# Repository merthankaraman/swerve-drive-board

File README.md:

# Swerve Drive Mobile Robot Board
### Schematic Of the Shield V2
<br/><br/>

### Board Of the Shield V2
<br/><br/>

### Schematic Of the Shield V1
<br/><br/>

### Board Of the Shield V1
<br/><br/>

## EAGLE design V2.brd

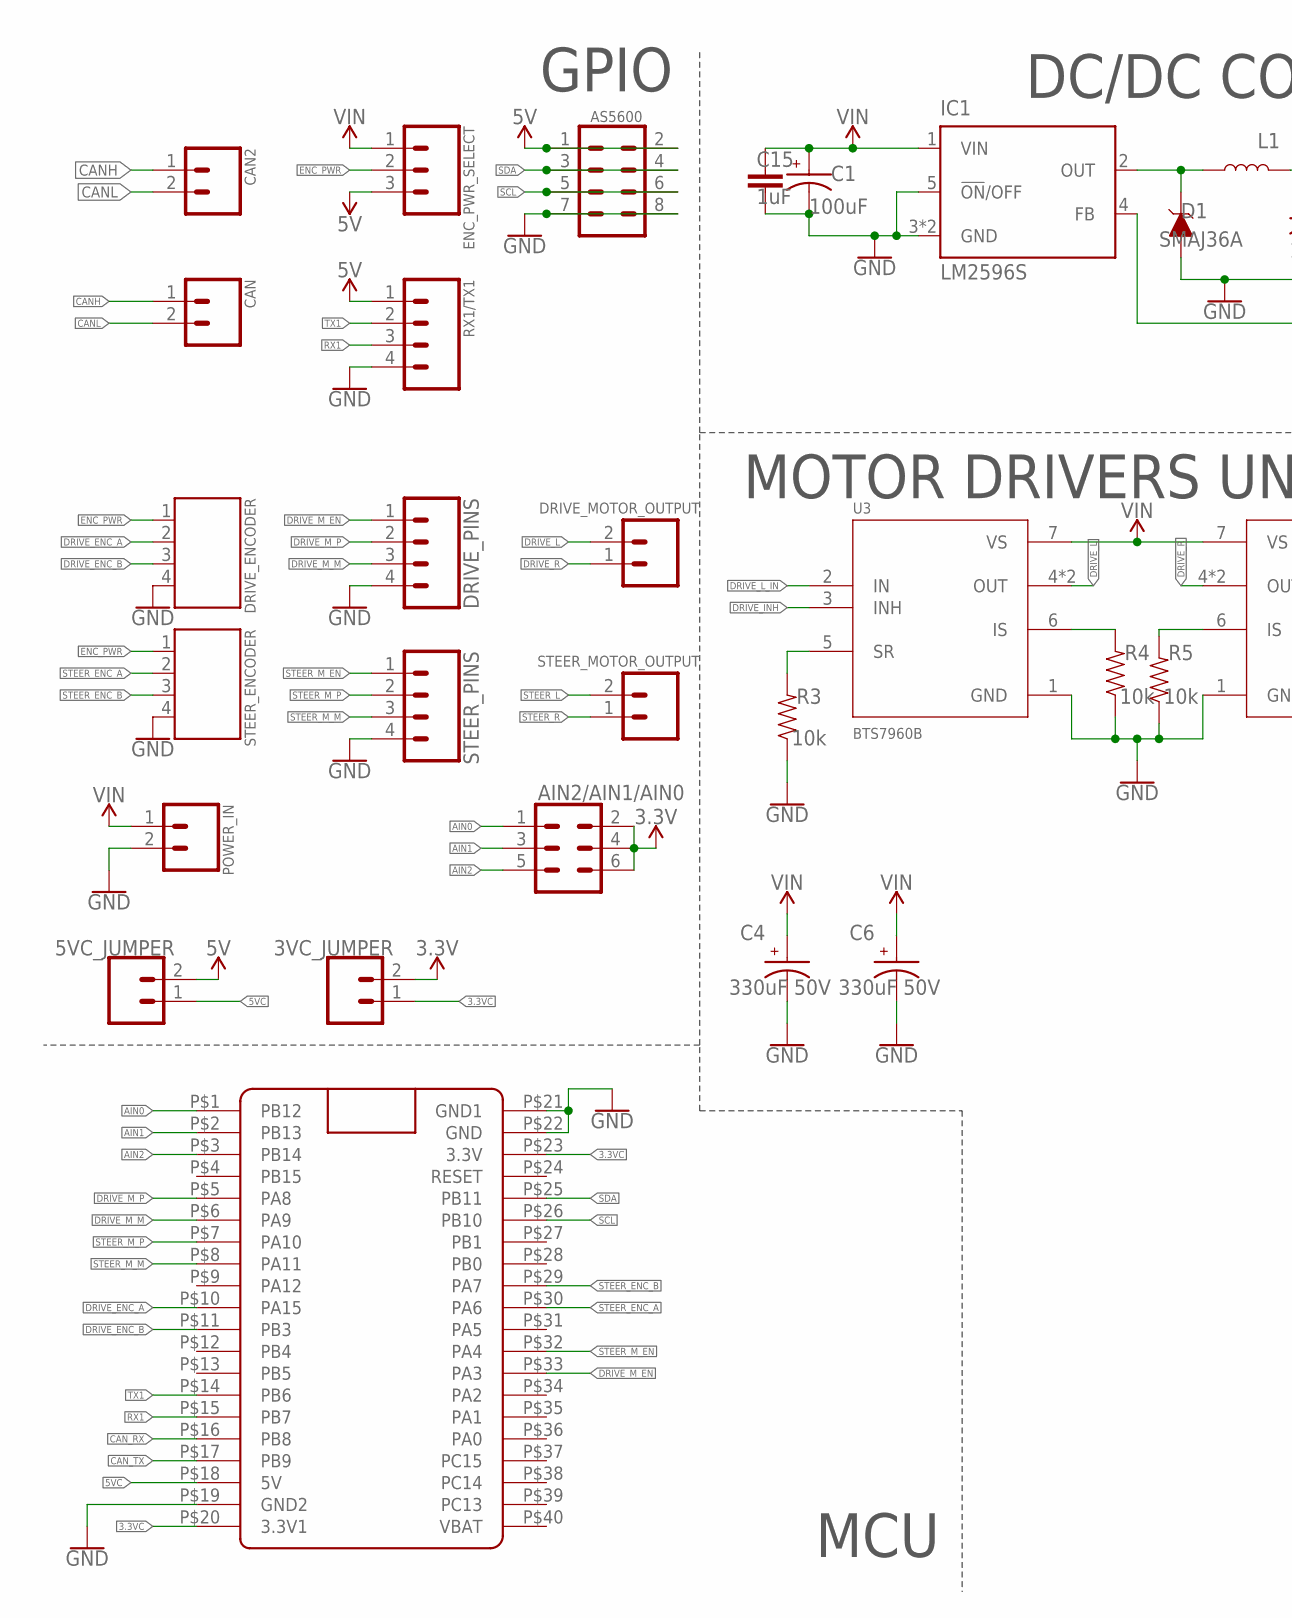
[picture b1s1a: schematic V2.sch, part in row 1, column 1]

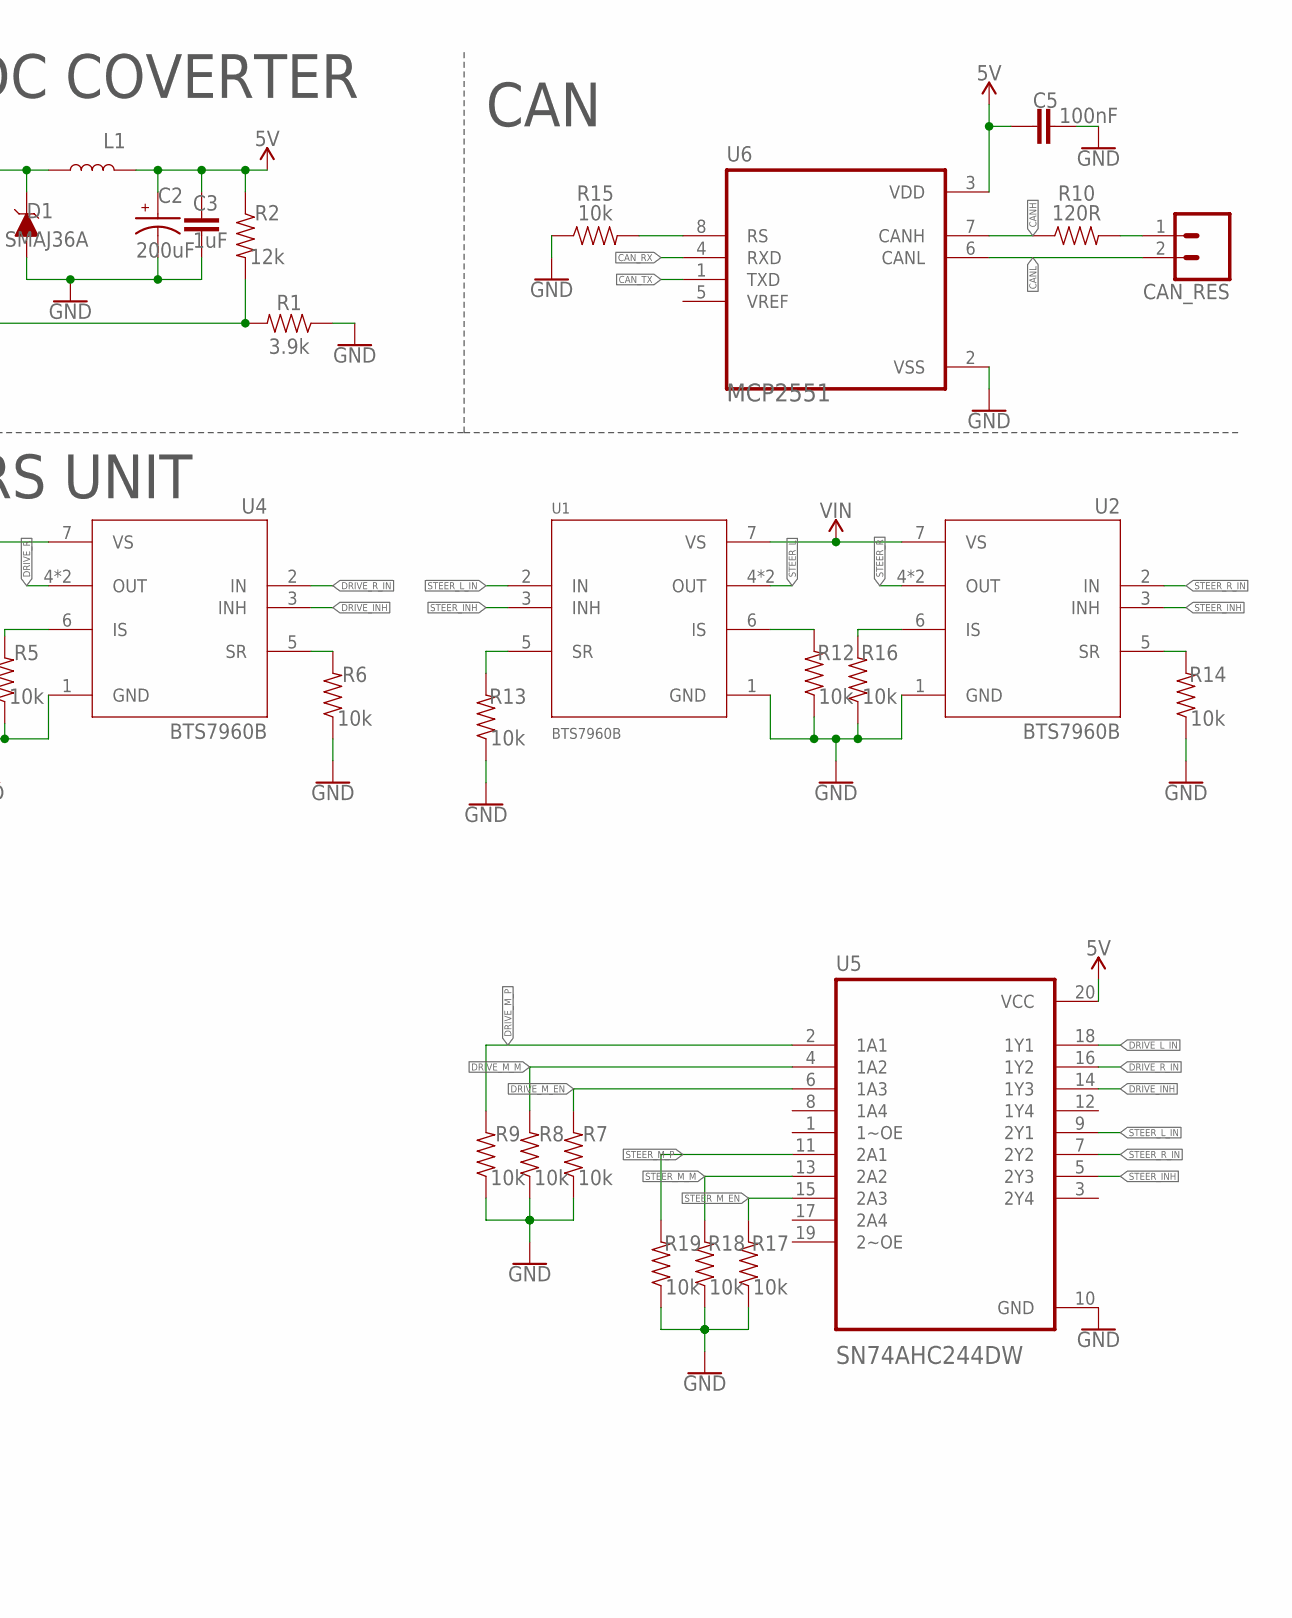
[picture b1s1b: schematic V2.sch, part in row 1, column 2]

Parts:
3VC_JUMPER, 5VC_JUMPER: CONN_02; 1X02
AIN2/AIN1/AIN0: CONN_03X2FEMALE; 2X3
AS5600: 5V/SCL/SDA/GND; 2X4
C1: 100uF; CPOL-SMD
C2: 200uF; CPOL-SMD
C3: 1uF; 0603
C4, C6: 330uF 50V; CPOL-RADIAL-5MM-10MM
C5: 100nF; 0805
C15: 1uF; 0805
CAN, CAN2: CANH/CANL; 5.08MM_2PIN
CAN_RES: CONN_02; 1X02
D1: SMAJ36A; DO-214AC
DRIVE_ENCODER: GND/B/A/PWR; 5.08MM_4PIN
DRIVE_MOTOR_OUTPUT: 5.08MM_2PIN
DRIVE_PINS: EN/ PWM_P/ PWM_M/ GND; 1X04
ENC_PWR_SELECT: VIN/PWR/5V; 1X03
IC1: LM2596S; TO263-5
L1: 47uH; COIL_14X14
POWER_IN: VIN/GND; 5.08MM_2PIN
R1: 3.9k; 0805
R2: 12k; 0805
R3, R4, R5, R6, R7, R8, R9, R12, R13, R14, R15, R16, R17, R18, R19: 10k; 0805
R10: 120R; 0805
RX1/TX1: GND/RX1/TX1/5V; 1X04
STEER_ENCODER: PWR/A/B/GND; 5.08MM_4PIN
STEER_MOTOR_OUTPUT: 5.08MM_2PIN
STEER_PINS: EN/ PWM_P/ PWM_M/ GND; 1X04
U1, U2, U3, U4: BTS7960B; DPAK127P1490X440-8N
U5: SN74AHC244DW; SOIC127P1030X265-20N
U6: MCP2551; DIP-8
U$1: BLUE_PILL

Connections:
3.3V: 3VC_JUMPER.2, AIN2/AIN1/AIN0.2, AIN2/AIN1/AIN0.4, AIN2/AIN1/AIN0.6
3.3VC: 3VC_JUMPER.1, U$1.P$20 (3.3V1), U$1.P$23 (3.3V)
5V: 5VC_JUMPER.2, AS5600.1, AS5600.2, C2.1, C3.2, C5.2, ENC_PWR_SELECT.3, L1.P$2 (2), R2.1, RX1/TX1.1, U5.20 (VCC), U6.3 (VDD)
5VC: 5VC_JUMPER.1, U$1.P$18 (5V)
AIN0: AIN2/AIN1/AIN0.1, U$1.P$1 (PB12)
AIN1: AIN2/AIN1/AIN0.3, U$1.P$2 (PB13)
AIN2: AIN2/AIN1/AIN0.5, U$1.P$3 (PB14)
CANH: CAN.1, CAN2.1, R10.1, U6.7 (CANH)
CANL: CAN.2, CAN2.2, CAN_RES.2, U6.6 (CANL)
CAN_RX: U6.4 (RXD), U$1.P$16 (PB8)
CAN_TX: U6.1 (TXD), U$1.P$17 (PB9)
DRIVE_ENC_A: DRIVE_ENCODER.2, U$1.P$10 (PA15)
DRIVE_ENC_B: DRIVE_ENCODER.3, U$1.P$11 (PB3)
DRIVE_INH: U3.3 (INH), U4.3 (INH), U5.14 (1Y3)
DRIVE_L: DRIVE_MOTOR_OUTPUT.2, U3.4 (OUT), U3.8 (OUT)
DRIVE_L_IN: U3.2 (IN), U5.18 (1Y1)
DRIVE_M_EN: DRIVE_PINS.1, R7.2, U5.6 (1A3), U$1.P$33 (PA3)
DRIVE_M_M: DRIVE_PINS.3, R8.2, U5.4 (1A2), U$1.P$6 (PA9)
DRIVE_M_P: DRIVE_PINS.2, R9.2, U5.2 (1A1), U$1.P$5 (PA8)
DRIVE_R: DRIVE_MOTOR_OUTPUT.1, U4.4 (OUT), U4.8 (OUT)
DRIVE_R_IN: U4.2 (IN), U5.16 (1Y2)
ENC_PWR: DRIVE_ENCODER.1, ENC_PWR_SELECT.2, STEER_ENCODER.1
GND: AS5600.7, AS5600.8, C1.2, C2.2, C3.1, C4.N, C5.1, C6.N, C15.1, D1.A, DRIVE_ENCODER.4, DRIVE_PINS.4, IC1.3 (GND), IC1.5 (!ON!/OFF), IC1.TAB (GND), POWER_IN.2, R1.1, R3.1, R4.1, R5.1, R6.1, R7.1, R8.1, R9.1, R12.1, R13.1, R14.1, R15.1, R16.1, R17.1, R18.1, R19.1, RX1/TX1.4, STEER_ENCODER.4, STEER_PINS.4, U1.1 (GND), U2.1 (GND), U3.1 (GND), U4.1 (GND), U5.10 (GND), U6.2 (VSS), U$1.P$19 (GND2), U$1.P$21 (GND1), U$1.P$22 (GND)
unnamed: D1.C, IC1.2 (OUT), L1.P$1 (1)
unnamed: IC1.4 (FB), R1.2, R2.2
unnamed: R14.2, U2.5 (SR)
unnamed: R16.2, U2.6 (IS)
unnamed: CAN_RES.1, R10.2
unnamed: R6.2, U4.5 (SR)
unnamed: R5.2, U4.6 (IS)
unnamed: R4.2, U3.6 (IS)
unnamed: R3.2, U3.5 (SR)
unnamed: R12.2, U1.6 (IS)
unnamed: R13.2, U1.5 (SR)
unnamed: R15.2, U6.8 (RS)
RX1: RX1/TX1.3, U$1.P$15 (PB7)
SCL: AS5600.5, AS5600.6, U$1.P$26 (PB10)
SDA: AS5600.3, AS5600.4, U$1.P$25 (PB11)
STEER_ENC_A: STEER_ENCODER.2, U$1.P$30 (PA6)
STEER_ENC_B: STEER_ENCODER.3, U$1.P$29 (PA7)
STEER_INH: U1.3 (INH), U2.3 (INH), U5.5 (2Y3)
STEER_L: STEER_MOTOR_OUTPUT.2, U1.4 (OUT), U1.8 (OUT)
STEER_L_IN: U1.2 (IN), U5.9 (2Y1)
STEER_M_EN: R17.2, STEER_PINS.1, U5.15 (2A3), U$1.P$32 (PA4)
STEER_M_M: R18.2, STEER_PINS.3, U5.13 (2A2), U$1.P$8 (PA11)
STEER_M_P: R19.2, STEER_PINS.2, U5.11 (2A1), U$1.P$7 (PA10)
STEER_R: STEER_MOTOR_OUTPUT.1, U2.4 (OUT), U2.8 (OUT)
STEER_R_IN: U2.2 (IN), U5.7 (2Y2)
TX1: RX1/TX1.2, U$1.P$14 (PB6)
VIN: C1.1, C4.P, C6.P, C15.2, ENC_PWR_SELECT.1, IC1.1 (VIN), POWER_IN.1, U1.7 (VS), U2.7 (VS), U3.7 (VS), U4.7 (VS)

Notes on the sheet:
MCU
CAN
DC/DC COVERTER
GPIO
MOTOR DRIVERS UNIT

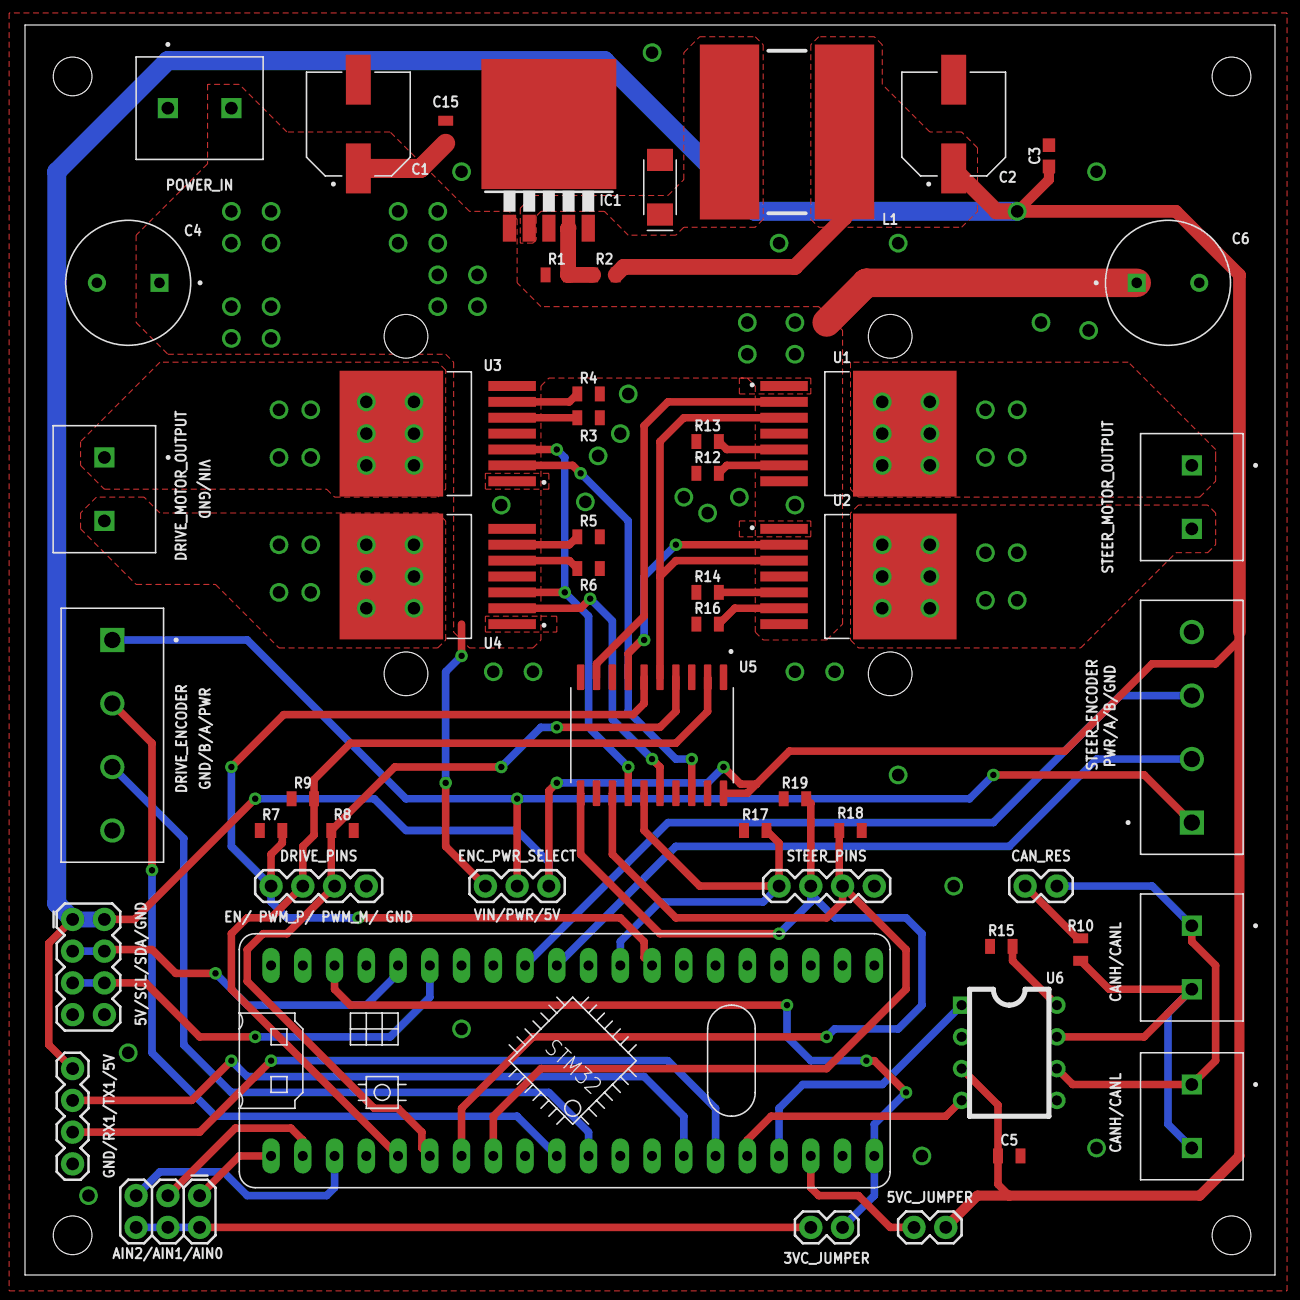
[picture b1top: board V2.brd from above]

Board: 2 copper layers, 100.0 x 100.0 mm, 53 parts (0 on the bottom side), 50 nets.

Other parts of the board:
U$2, U$3: BTS_HEATER

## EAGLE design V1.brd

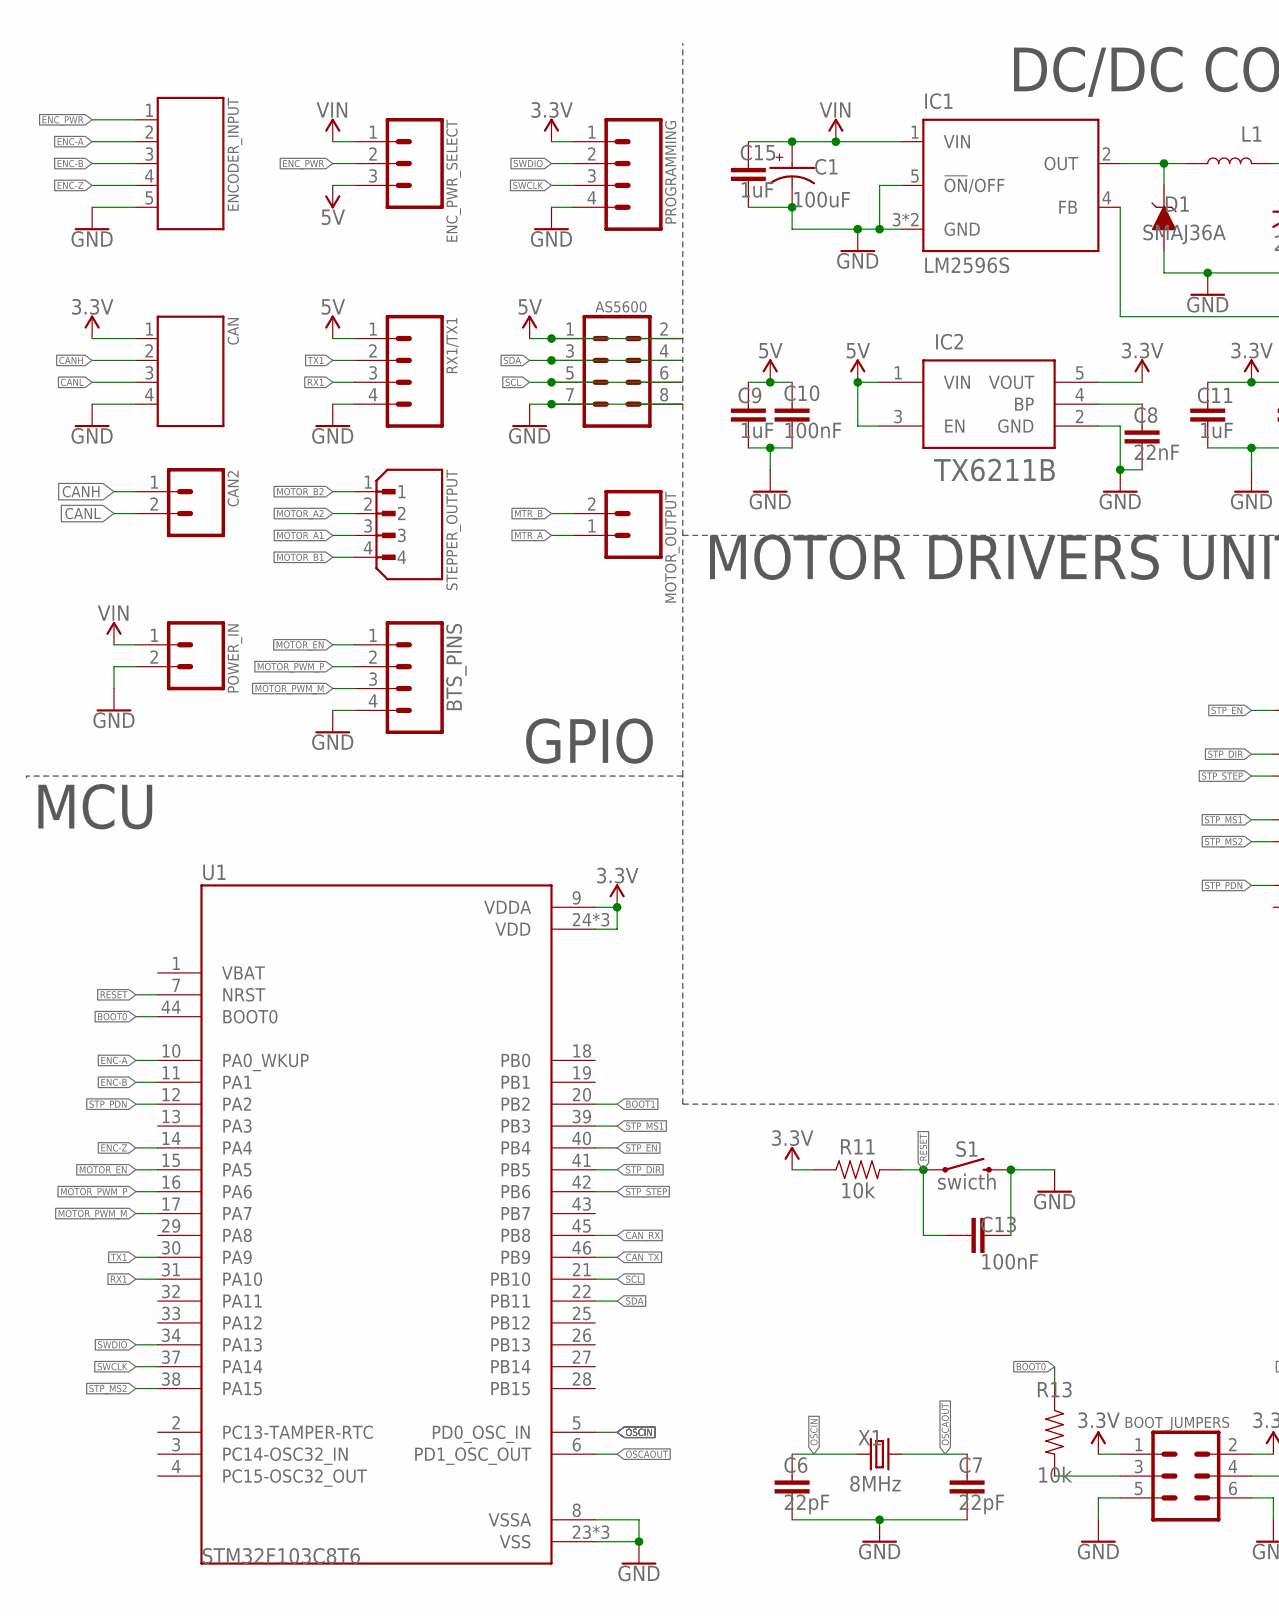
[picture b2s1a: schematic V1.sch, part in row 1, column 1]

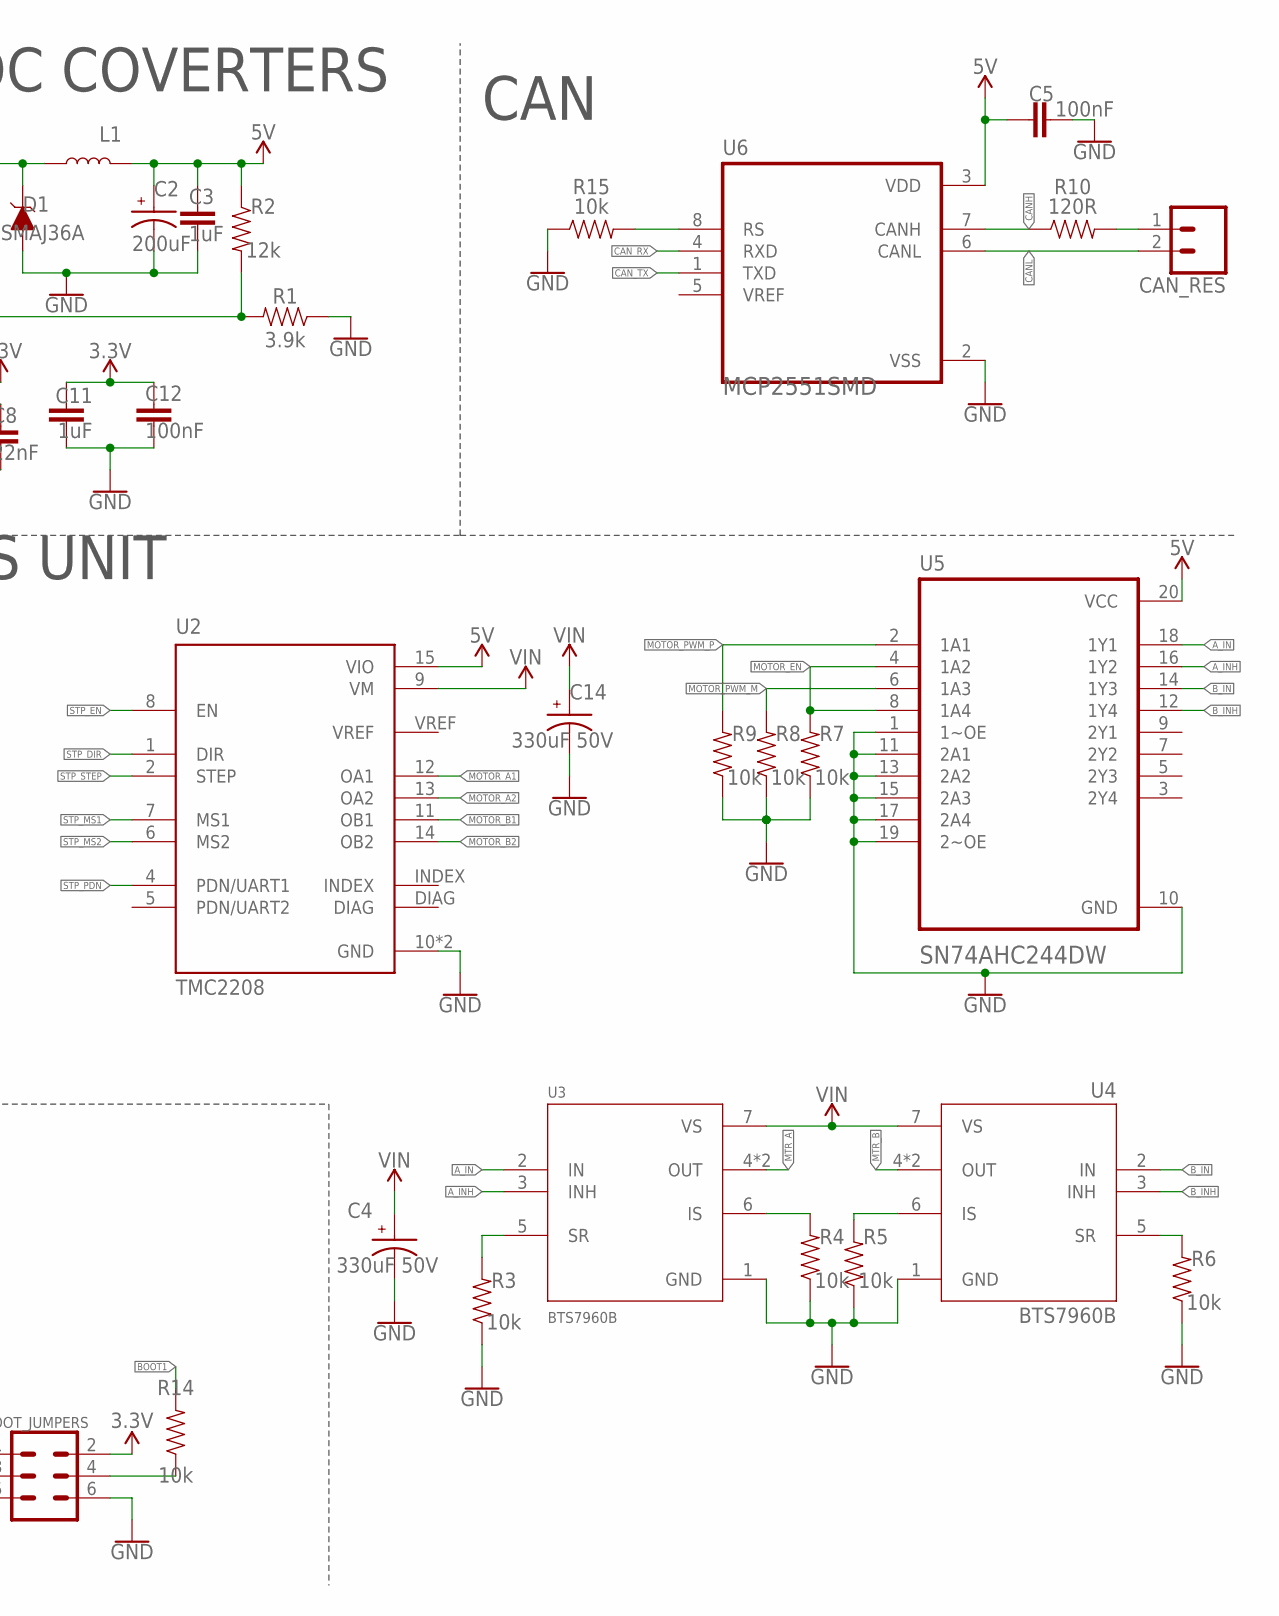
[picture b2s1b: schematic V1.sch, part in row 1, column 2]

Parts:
AS5600: 5V/SDA/SCL/GND; 2X4
BOOT_JUMPERS: CONN_03X2FEMALE; 2X3
BTS_PINS: GND/ PWM_M/ PWM_P/ EN; 1X04
C1: 100uF; CPOL-SMD
C2: 200uF; CPOL-SMD
C3: 1uF; 0603
C4, C14: 330uF 50V; CPOL-RADIAL-5MM-10MM
C5, C10, C12, C13: 100nF; 0805
C6, C7: 22pF; 0805
C8: 22nF; 0805
C9, C11, C15: 1uF; 0805
CAN: 3.3V/CANH/CANL/GND; 5.08MM_4PIN
CAN2: CANH/CANL; 5.08MM_2PIN
CAN_RES: CONN_02; 1X02
D1: SMAJ36A; DO-214AC
ENCODER_INPUT: PWR/A/B/Z/GND; 5.08MM_5PIN
ENC_PWR_SELECT: VIN/PWR/5V; 1X03
IC1: LM2596S; TO263-5
IC2: TX6211B; SOT23-5
L1: 47uH; COIL_14X14
MOTOR_OUTPUT: 5.08MM_2PIN
POWER_IN: VIN/GND; 5.08MM_2PIN
PROGRAMMING: 3.3V/SWDIO/SWCLK/GND; 1X04
R1: 3.9k; 0805
R2: 12k; 0805
R3, R4, R5, R6, R7, R8, R9, R11, R13, R14, R15: 10k; 0805
R10: 120R; 0805
RX1/TX1: 5V/TX1/RX1/GND; 1X04
S1: swicth; TACTILE_SWITCH_SMD_5.2MM
STEPPER_OUTPUT: 4PIN_TUNIC_2.5MM; JST_B4B-XH-A(LF)(SN)
U1: STM32F103C8T6; LQFP-48
U2: TMC2208; MODULE_TMC2208_SILENTSTEPSTICK
U3, U4: BTS7960B; DPAK127P1490X440-8N
U5: SN74AHC244DW; SOIC127P1030X265-20N
U6: MCP2551SMD; SOIC-8
X1: 8MHz; HC49

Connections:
3.3V: BOOT_JUMPERS.1, BOOT_JUMPERS.2, C11.2, C12.2, CAN.1, IC2.5 (VOUT), PROGRAMMING.1, R11.1, U1.9 (VDDA), U1.24 (VDD), U1.36 (VDD), U1.48 (VDD)
5V: AS5600.1, AS5600.2, C2.1, C3.2, C5.2, C9.2, C10.2, ENC_PWR_SELECT.3, IC2.1 (VIN), IC2.3 (EN), L1.P$2 (2), R2.1, RX1/TX1.1, U2.15 (VIO), U5.20 (VCC), U6.3 (VDD)
A_IN: U3.2 (IN), U5.18 (1Y1)
A_INH: U3.3 (INH), U5.16 (1Y2)
BOOT0: R13.1, U1.44 (BOOT0)
BOOT1: R14.2, U1.20 (PB2)
B_IN: U4.2 (IN), U5.14 (1Y3)
B_INH: U4.3 (INH), U5.12 (1Y4)
CANH: CAN.2, CAN2.1, R10.1, U6.7 (CANH)
CANL: CAN.3, CAN2.2, CAN_RES.2, U6.6 (CANL)
CAN_RX: U1.45 (PB8), U6.4 (RXD)
CAN_TX: U1.46 (PB9), U6.1 (TXD)
ENC-A: ENCODER_INPUT.2, U1.10 (PA0_WKUP)
ENC-B: ENCODER_INPUT.3, U1.11 (PA1)
ENC-Z: ENCODER_INPUT.4, U1.14 (PA4)
ENC_PWR: ENCODER_INPUT.1, ENC_PWR_SELECT.2
GND: AS5600.7, AS5600.8, BOOT_JUMPERS.5, BOOT_JUMPERS.6, BTS_PINS.4, C1.2, C2.2, C3.1, C4.N, C5.1, C6.1, C7.1, C8.1, C9.1, C10.1, C11.1, C12.1, C13.1, C14.N, C15.1, CAN.4, D1.A, ENCODER_INPUT.5, IC1.3 (GND), IC1.5 (!ON!/OFF), IC1.TAB (GND), IC2.2 (GND), POWER_IN.2, PROGRAMMING.4, R1.1, R3.1, R4.1, R5.1, R6.1, R7.1, R8.1, R9.1, R15.1, RX1/TX1.4, S1.3 (2), U1.8 (VSSA), U1.23 (VSS), U1.35 (VSS), U1.47 (VSS), U2.10 (GND), U2.16 (GND), U3.1 (GND), U4.1 (GND), U5.1 (1~OE), U5.10 (GND), U5.11 (2A1), U5.13 (2A2), U5.15 (2A3), U5.17 (2A4), U5.19 (2~OE), U6.2 (VSS)
MOTOR_A1: STEPPER_OUTPUT.3, U2.12 (OA1)
MOTOR_A2: STEPPER_OUTPUT.2, U2.13 (OA2)
MOTOR_B1: STEPPER_OUTPUT.4, U2.11 (OB1)
MOTOR_B2: STEPPER_OUTPUT.1, U2.14 (OB2)
MOTOR_EN: BTS_PINS.1, R7.2, U1.15 (PA5), U5.4 (1A2), U5.8 (1A4)
MOTOR_PWM_M: BTS_PINS.3, R8.2, U1.17 (PA7), U5.6 (1A3)
MOTOR_PWM_P: BTS_PINS.2, R9.2, U1.16 (PA6), U5.2 (1A1)
MTR_A: MOTOR_OUTPUT.1, U3.4 (OUT), U3.8 (OUT)
MTR_B: MOTOR_OUTPUT.2, U4.4 (OUT), U4.8 (OUT)
unnamed: D1.C, IC1.2 (OUT), L1.P$1 (1)
unnamed: IC1.4 (FB), R1.2, R2.2
unnamed: CAN_RES.1, R10.2
unnamed: R6.2, U4.5 (SR)
unnamed: R5.2, U4.6 (IS)
unnamed: R4.2, U3.6 (IS)
unnamed: R3.2, U3.5 (SR)
unnamed: C8.2, IC2.4 (BP)
unnamed: BOOT_JUMPERS.4, R14.1
unnamed: R15.2, U6.8 (RS)
unnamed: BOOT_JUMPERS.3, R13.2
OSCAOUT: C7.2, U1.6 (PD1_OSC_OUT), X1.2
OSCIN: C6.2, U1.5 (PD0_OSC_IN), X1.1
RESET: C13.2, R11.2, S1.1, U1.7 (NRST)
RX1: RX1/TX1.3, U1.31 (PA10)
SCL: AS5600.5, AS5600.6, U1.21 (PB10)
SDA: AS5600.3, AS5600.4, U1.22 (PB11)
STP_DIR: U1.41 (PB5), U2.1 (DIR)
STP_EN: U1.40 (PB4), U2.8 (EN)
STP_MS1: U1.39 (PB3), U2.7 (MS1)
STP_MS2: U1.38 (PA15), U2.6 (MS2)
STP_PDN: U1.12 (PA2), U2.4 (PDN/UART1)
STP_STEP: U1.42 (PB6), U2.2 (STEP)
SWCLK: PROGRAMMING.3, U1.37 (PA14)
SWDIO: PROGRAMMING.2, U1.34 (PA13)
TX1: RX1/TX1.2, U1.30 (PA9)
VIN: C1.1, C4.P, C14.P, C15.2, ENC_PWR_SELECT.1, IC1.1 (VIN), POWER_IN.1, U2.9 (VM), U3.7 (VS), U4.7 (VS)

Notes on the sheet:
MCU
CAN
DC/DC COVERTERS
GPIO
MOTOR DRIVERS UNIT

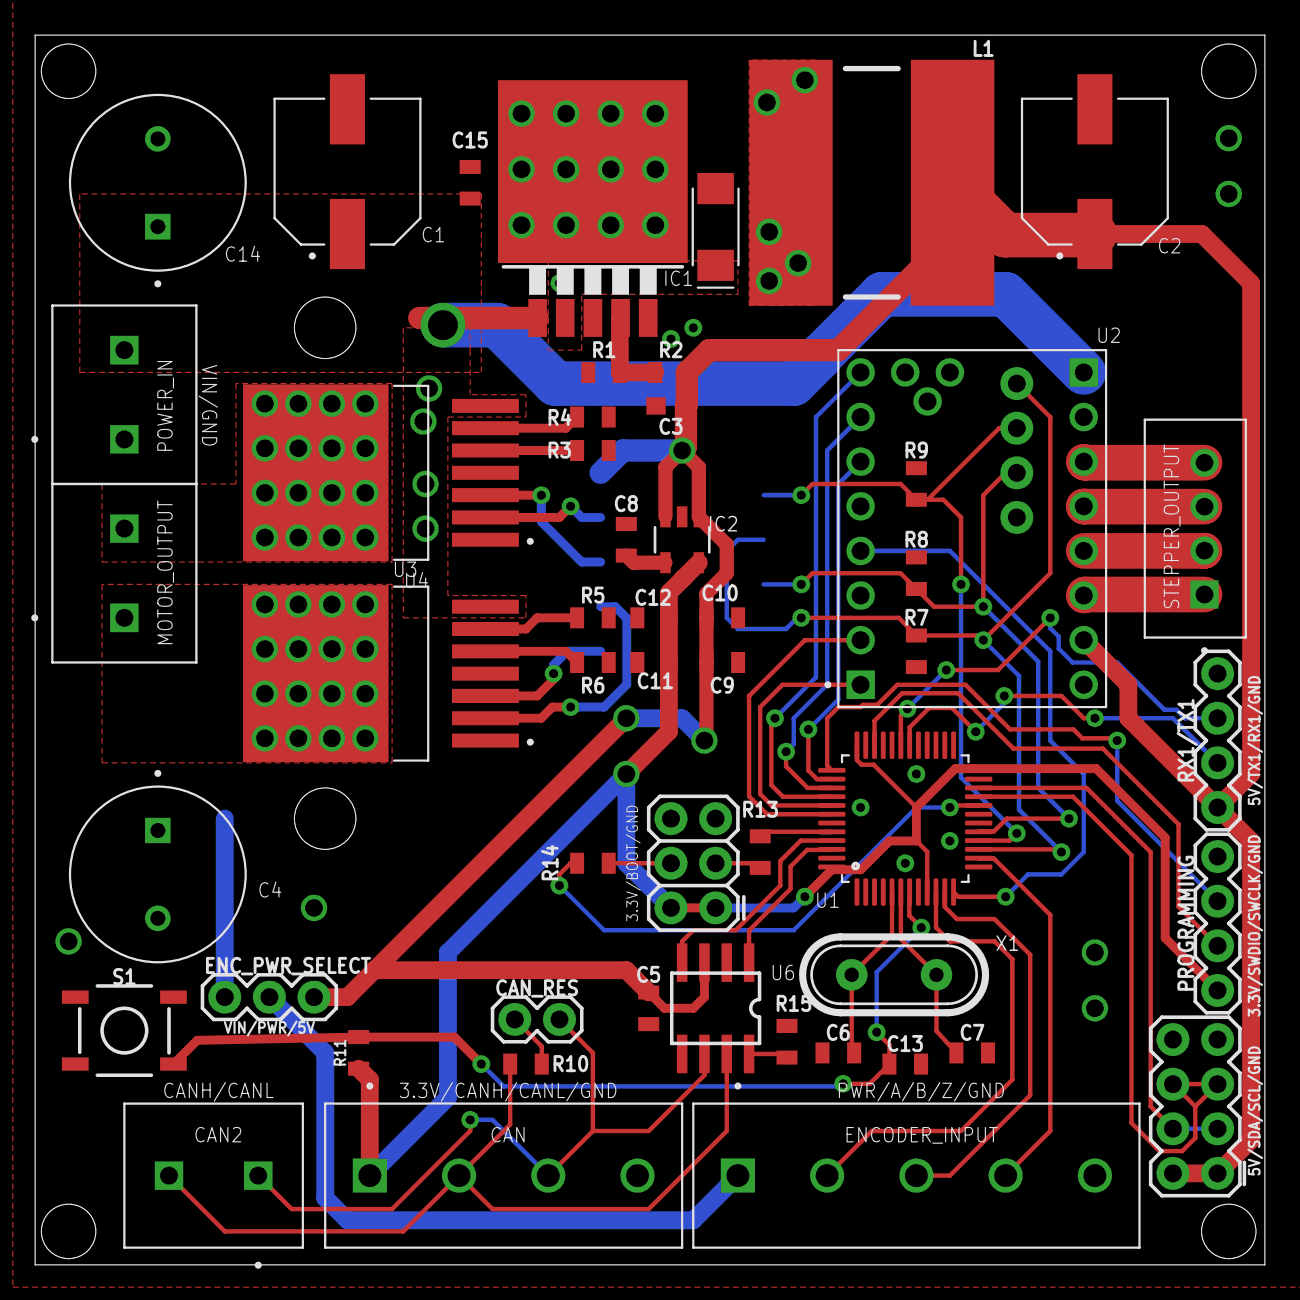
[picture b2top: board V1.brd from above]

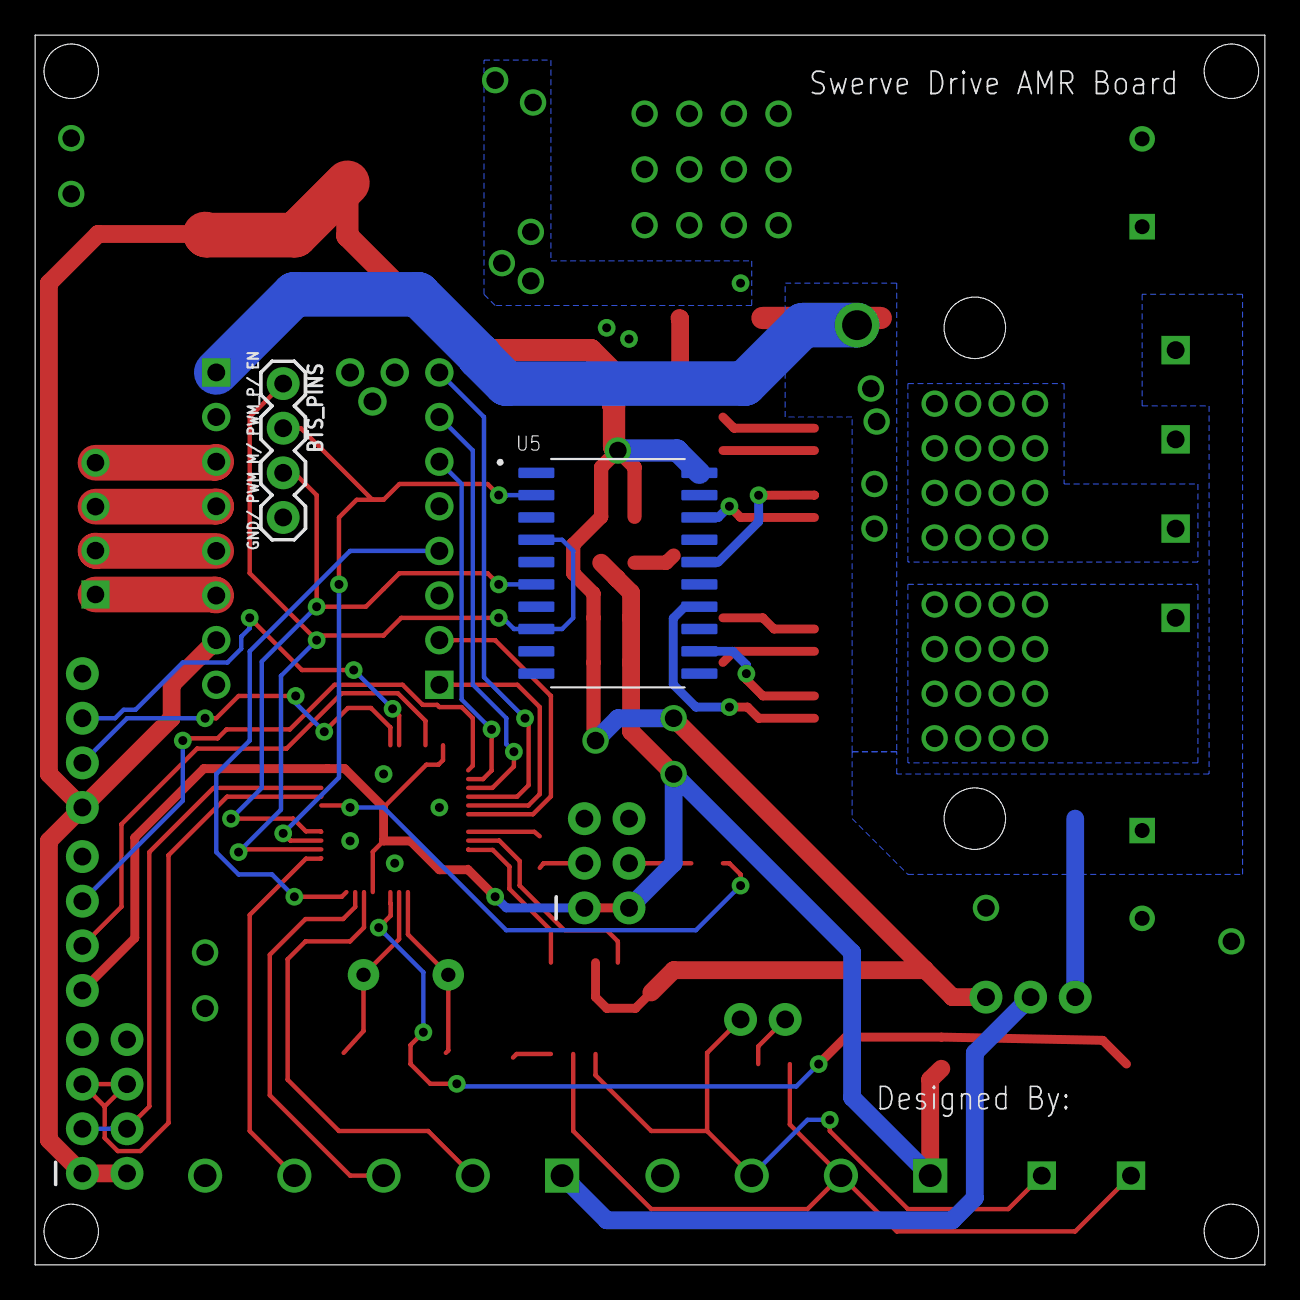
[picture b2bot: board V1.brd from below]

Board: 2 copper layers, 70.0 x 70.0 mm, 54 parts (2 on the bottom side), 53 nets.

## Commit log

2023-06-21 Almost ended V2. Review required
2023-06-22 V2 finished
2023-06-24 Fixed minor design problems

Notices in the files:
parts and their libraries:
SparkFun-Capacitors: Licensing: Creative Commons ShareAlike 4.0 International - https://creativecommons.org/licenses/by-sa/4.0
